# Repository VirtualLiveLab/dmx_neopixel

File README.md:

# dmx neopixel
DMX信号をNeoPixelの信号に変換する基板

## 基板設計
- KiCad 9.0で作成
- [JLCPCB](https://jlcpcb.com)に発注
- 部品はほぼ全て秋月電子通商にて購入可能(XLRのレセプタクルのみサウンドハウスで購入)

## ファームウェア書き込み
- [PlatformIO Core](https://docs.platformio.org/en/latest/core/index.html)をインストール
  - [get-platformio.py](https://raw.githubusercontent.com/platformio/platformio-core-installer/master/get-platformio.py)をダウンロードしてPython3で実行
- USBで基板をPCに接続
- 書き込みコマンド実行

```bash
cd ./platformio/
pio run
```

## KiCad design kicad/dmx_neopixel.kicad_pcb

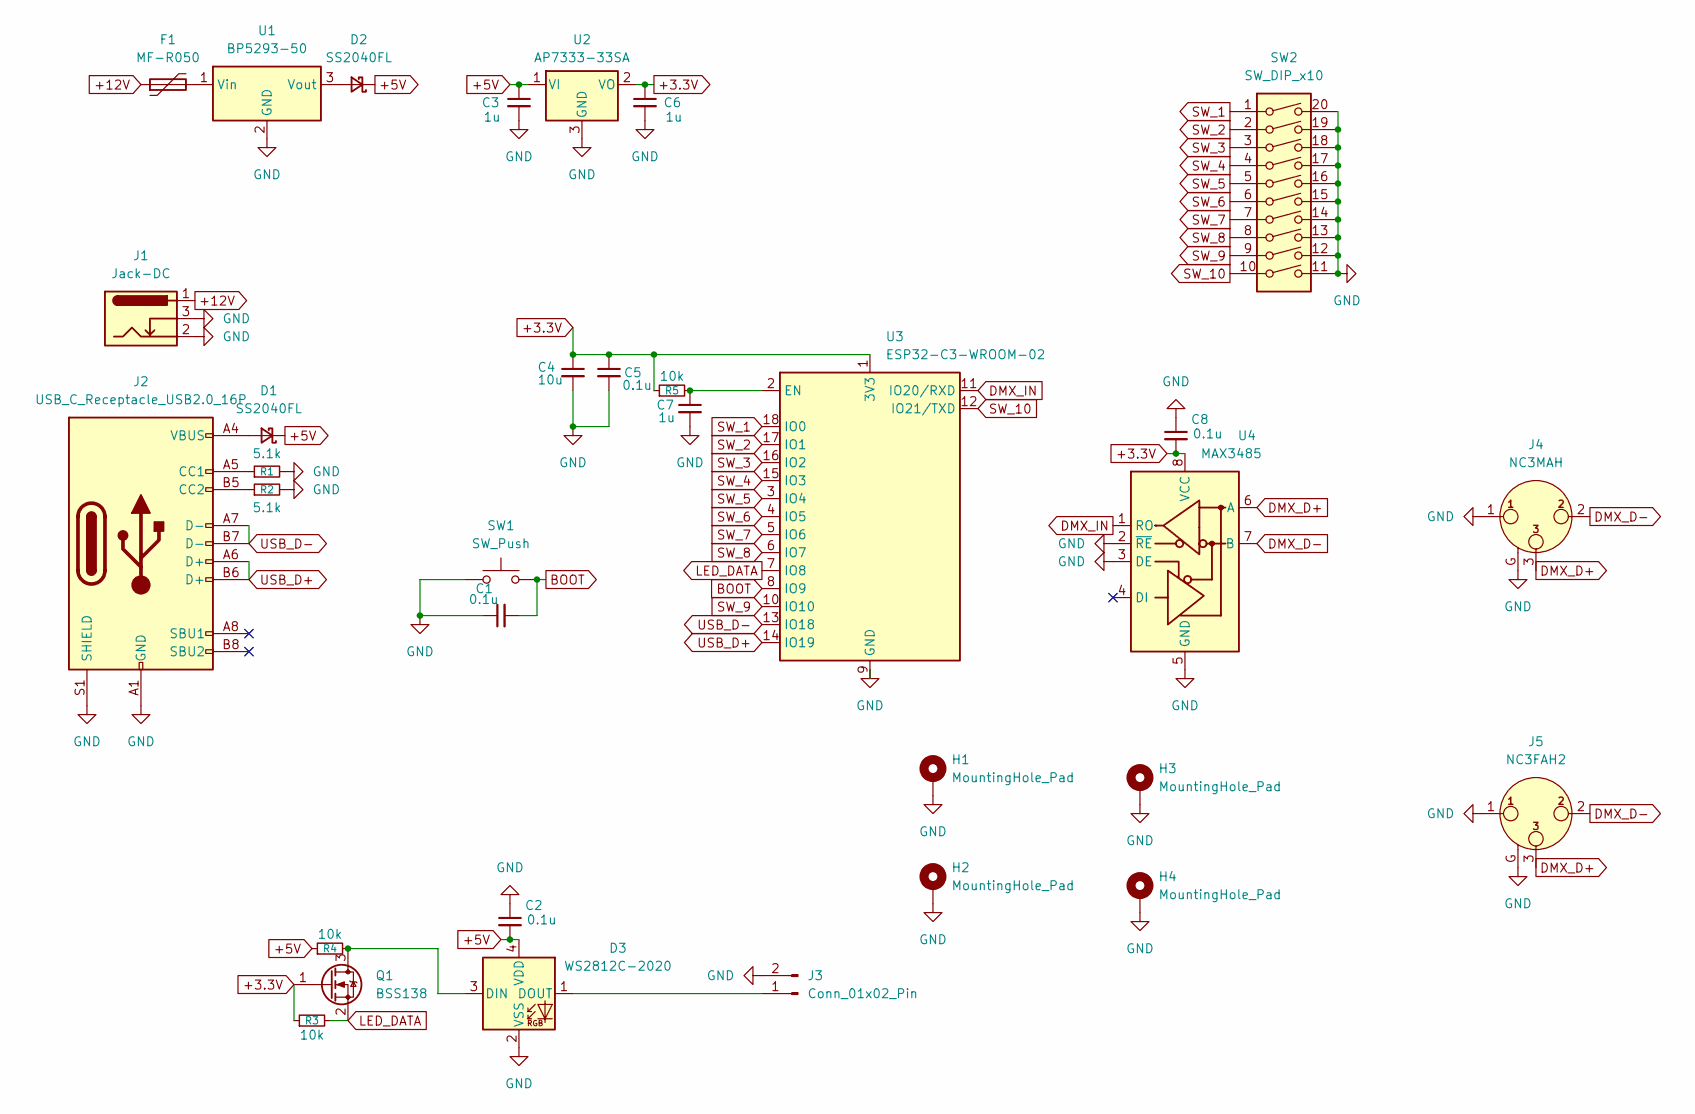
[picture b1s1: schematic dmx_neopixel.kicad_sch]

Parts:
C1, C2, C5, C8: 0.1u; C_0603_1608Metric_Pad1.08x0.95mm_HandSolder
C3, C6, C7: 1u; C_0603_1608Metric_Pad1.08x0.95mm_HandSolder
C4: 10u; C_0603_1608Metric_Pad1.08x0.95mm_HandSolder
D1, D2: SS2040FL; D_SOD-123F
D3: WS2812C-2020; LED_WS2812B-2020_PLCC4_2.0x2.0mm
F1: MF-R050; Fuse_Bourns_MF-RHT050
H1, H2, H3, H4: MountingHole_Pad; MountingHole_3.2mm_M3_Pad_TopBottom
J1: Jack-DC; BarrelJack_Horizontal
J2: USB_C_Receptacle_USB2.0_16P; USB_C_Receptacle_GCT_USB4105-xx-A_16P_TopMnt_Horizontal
J3: Conn_01x02_Pin; JST_XH_S2B-XH-A_1x02_P2.50mm_Horizontal
J4: NC3MAH; Jack_XLR_Neutrik_NC3MAH_Horizontal
J5: NC3FAH2; Jack_XLR_Neutrik_NC3FAH2_Horizontal
Q1: BSS138; SOT-23
R1, R2: 5.1k; R_0603_1608Metric_Pad0.98x0.95mm_HandSolder
R3, R4, R5: 10k; R_0603_1608Metric_Pad0.98x0.95mm_HandSolder
SW1: SW_Push; SW_SPST_PTS810
SW2: SW_DIP_x10; SW_DIP_SPSTx10_Slide_6.7x26.96mm_W7.62mm_P2.54mm_LowProfile
U1: BP5293-50; SIP3_11.6x8.5mm
U2: AP7333-33SA; SOT-23
U3: ESP32-C3-WROOM-02
U4: MAX3485; SOIC-8_3.9x4.9mm_P1.27mm

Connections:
+3.3V: C4.1, C5.1, C6.1, C8.2, Q1.1 (G), R3.1, R5.1, U2.2 (VO), U3.1 (3V3), U4.8 (VCC)
+5V: C2.2, C3.1, D1.1 (K), D2.1 (K), D3.4 (VDD), R4.1, U2.1 (VI)
+12V: F1.1, J1.1
BOOT: C1.2, SW1.2, U3.8 (IO9)
DMX_D+: J4.3, J5.3, U4.6 (A)
DMX_D-: J4.2, J5.2, U4.7 (B)
DMX_IN: U3.11 (IO20/RXD), U4.1 (RO)
GND: C1.1, C2.1, C3.2, C4.2, C5.2, C6.2, C7.2, C8.1, D3.2 (VSS), H1.1, H2.1, H3.1, H4.1, J1.2, J1.3, J2.A1 (GND), J2.A12 (GND), J2.B1 (GND), J2.B12 (GND), J2.S1 (SHIELD), J3.2, J4.1, J4.G, J5.1, J5.G, R1.2, R2.2, SW1.1, SW2.11, SW2.12, SW2.13, SW2.14, SW2.15, SW2.16, SW2.17, SW2.18, SW2.19, SW2.20, U1.2 (GND), U2.3 (GND), U3.9 (GND), U3.19 (GND), U4.2 (~RE), U4.3 (DE), U4.5 (GND)
LED_DATA: Q1.2 (S), R3.2, U3.7 (IO8)
unnamed: D1.2 (A), J2.A4 (VBUS), J2.A9 (VBUS), J2.B4 (VBUS), J2.B9 (VBUS)
unnamed: D2.2 (A), U1.3 (Vout)
unnamed: D3.3 (DIN), Q1.3 (D), R4.2
unnamed: D3.1 (DOUT), J3.1
unnamed: J2.A5 (CC1), R1.1
unnamed: J2.B5 (CC2), R2.1
unnamed: F1.2, U1.1 (Vin)
unnamed: C7.1, R5.2, U3.2 (EN)
SW_1: SW2.1, U3.18 (IO0)
SW_2: SW2.2, U3.17 (IO1)
SW_3: SW2.3, U3.16 (IO2)
SW_4: SW2.4, U3.15 (IO3)
SW_5: SW2.5, U3.3 (IO4)
SW_6: SW2.6, U3.4 (IO5)
SW_7: SW2.7, U3.5 (IO6)
SW_8: SW2.8, U3.6 (IO7)
SW_9: SW2.9, U3.10 (IO10)
SW_10: SW2.10, U3.12 (IO21/TXD)
USB_D+: J2.A6 (D+), J2.B6 (D+), U3.14 (IO19)
USB_D-: J2.A7 (D-), J2.B7 (D-), U3.13 (IO18)

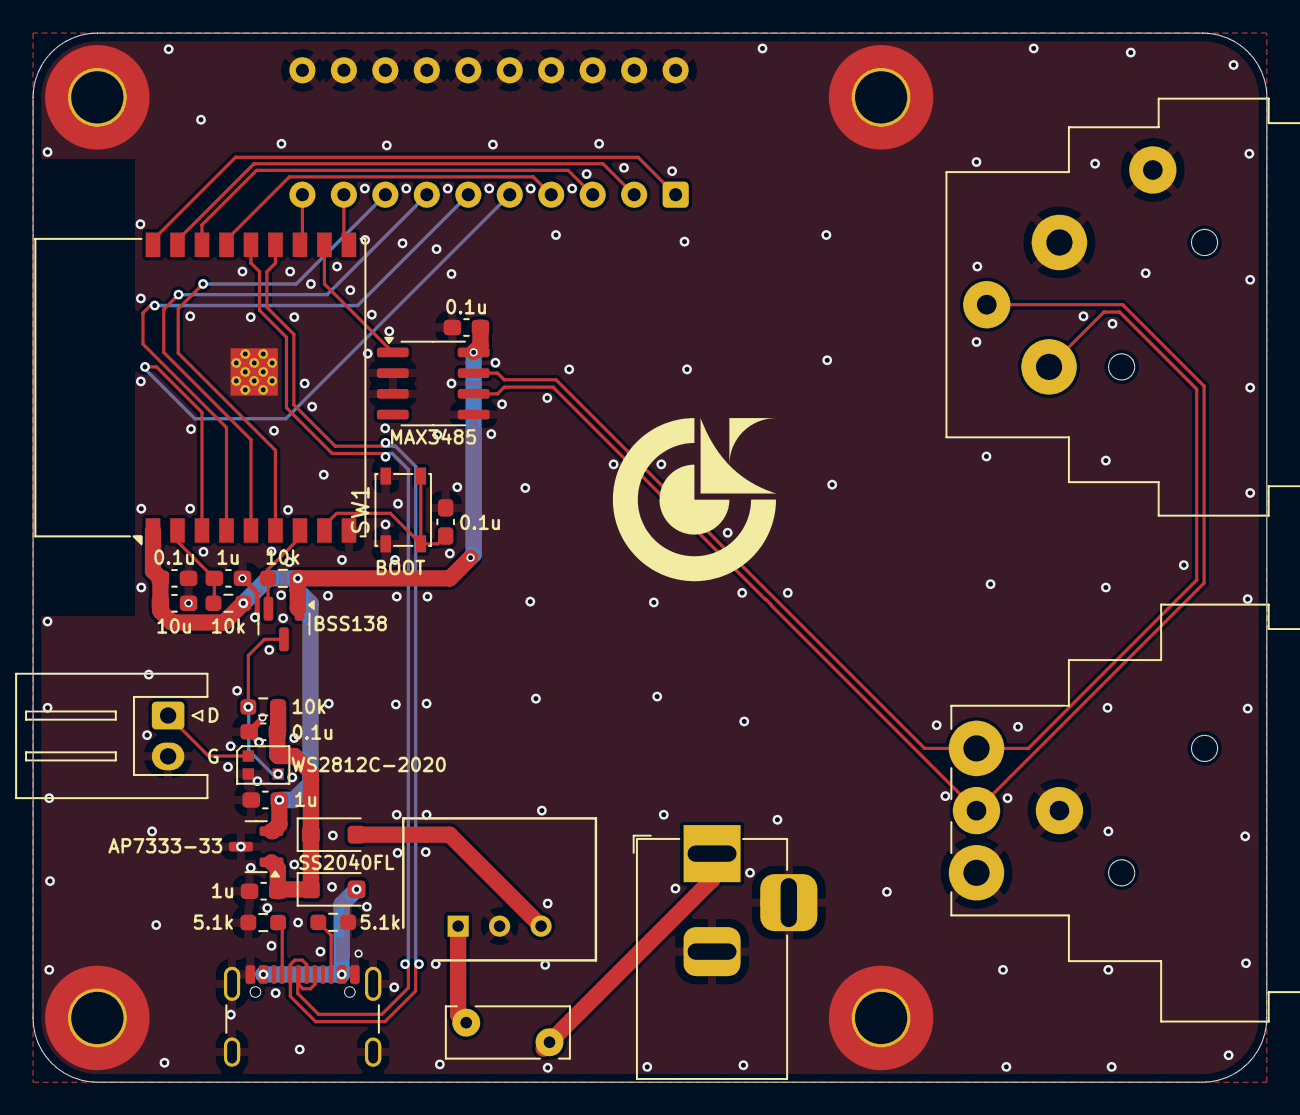
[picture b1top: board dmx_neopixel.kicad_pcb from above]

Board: 2 copper layers, 75.6 x 64.3 mm, 33 parts (1 on the bottom side), 29 nets.

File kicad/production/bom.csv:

Designator,Footprint,Quantity,Value,LCSC Part #
"C1, C2, C5, C8",0603,4,0.1u,
"C3, C6, C7",0603,3,1u,
C4,0603,1,10u,
"D1, D2",D_SOD-123F,2,SS2040FL,
D3,LED_WS2812B-2020_PLCC4_2.0x2.0mm,1,WS2812C-2020,
F1,Fuse_Bourns_MF-RHT050,1,MF-R050,
J1,BarrelJack_Horizontal,1,Jack-DC,
J2,USB_C_Receptacle_GCT_USB4105-xx-A_16P_TopMnt_Horizontal,1,USB_C_Receptacle_USB2.0_16P,
J3,JST_XH_S2B-XH-A_1x02_P2.50mm_Horizontal,1,Conn_01x02_Pin,
J4,Jack_XLR_Neutrik_NC3MAH_Horizontal,1,NC3MAH,
J5,Jack_XLR_Neutrik_NC3FAH2_Horizontal,1,NC3FAH2,
Q1,SOT-23,1,BSS138,
"R1, R2",0603,2,5.1k,
"R3, R4, R5",0603,3,10k,
SW1,SW_SPST_PTS810,1,SW_Push,
SW2,SW_DIP_SPSTx10_Slide_6.7x26.96mm_W7.62mm_P2.54mm_LowProfile,1,SW_DIP_x10,
U1,SIP3_11.6x8.5mm,1,BP5293-50,
U2,SOT-23,1,AP7333-33SA,
U3,ESP32-C3-WROOM-02,1,ESP32-C3-WROOM-02,
U4,SOIC-8_3.9x4.9mm_P1.27mm,1,MAX3485,

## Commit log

2025-05-10 feat: add kicad files
2025-05-28 feat: v0.2の基板を作成
2025-06-01 feat: 割り当ての設定方法を変更
2025-06-02 feat: 拡張子などを変更
2025-06-02 feat: 小変更
2025-06-02 feat: USBでのデバッグを無効にできるようにした
2025-06-02 fix: 構文エラー修正
2025-06-02 feat: コードの最適化
2025-06-02 feat: 不要なループを排除
2025-06-03 feat: インジケーターの明るさとテープの明るさを分離
2025-06-06 feat: ESP32をC3に変更
2025-06-19 feat: v1.0の基板データを追加
2025-06-19 feat: READMEを作成
2025-06-19 feat: update README
2025-06-19 feat: READMEを更新
2025-06-24 feat: 基板データ更新
2025-07-03 feat: PCから設定できるファームウェアを作成
2025-07-08 feat: パフォーマンス改善
2025-07-09 feat: ガンマ補正無効化
2025-07-10 feat: dmx処理の小修正
2025-07-10 feat: CRCの処理の最適化
